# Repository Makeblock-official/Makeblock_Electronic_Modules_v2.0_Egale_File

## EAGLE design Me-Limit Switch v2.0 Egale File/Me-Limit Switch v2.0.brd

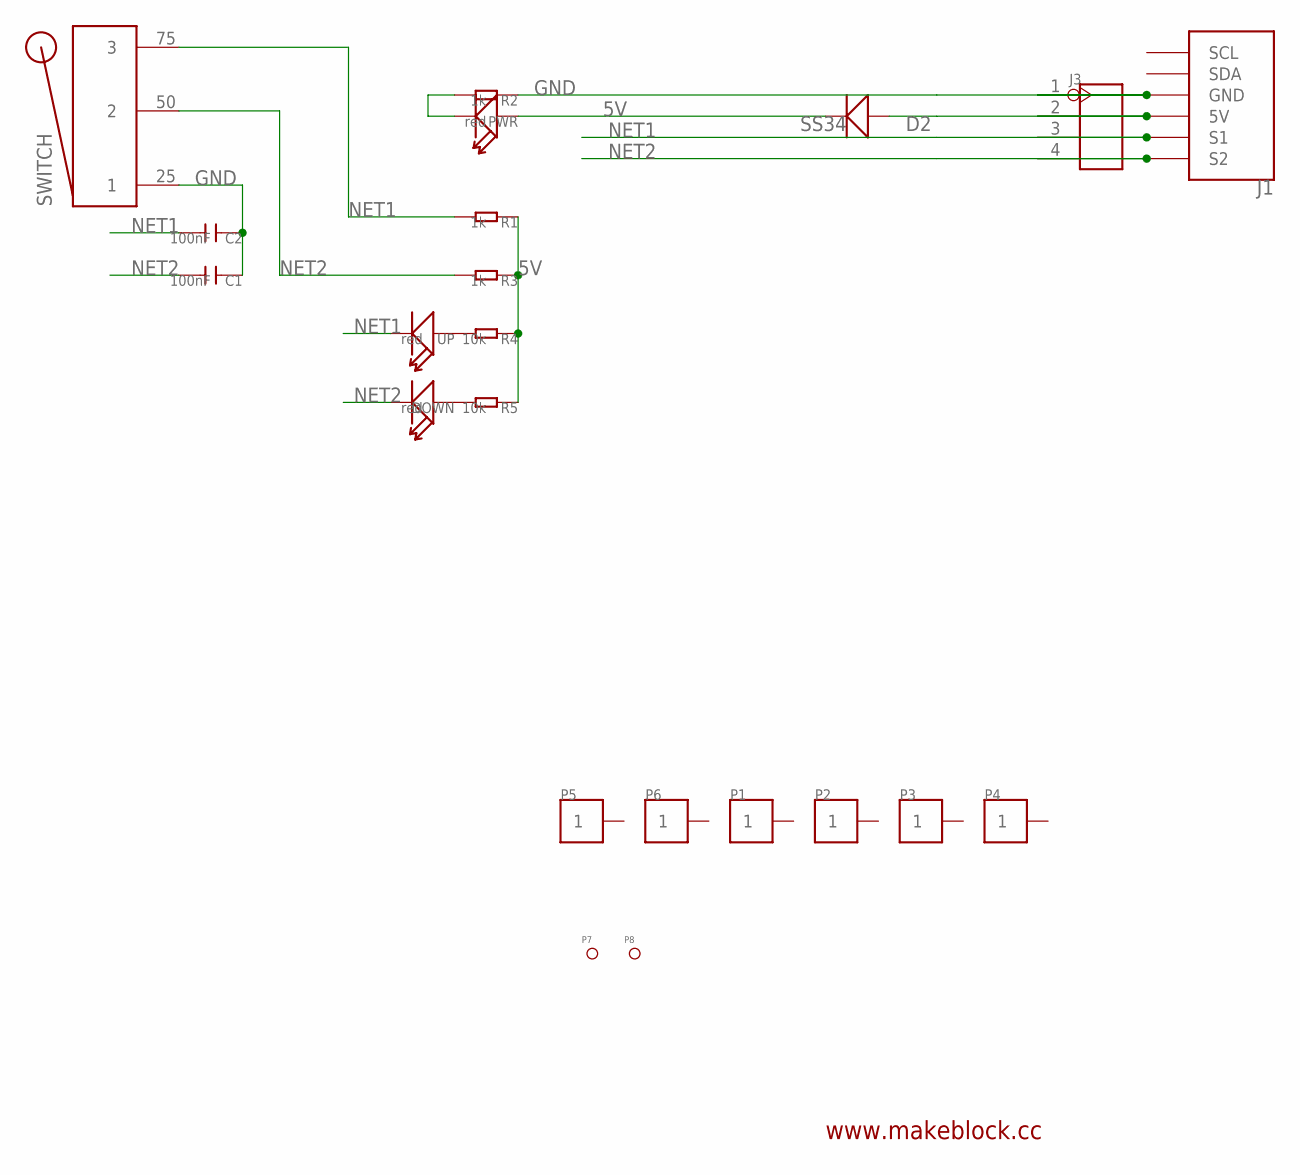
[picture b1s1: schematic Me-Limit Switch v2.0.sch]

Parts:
C1, C2: 100nF; 0603
D2: SS34; D2010
DOWN: red; LED-0603
J1: RJ11-6P6C-DIGI; RJ11-6P6C
J3: HEADER-4P-60/35MIL; 4P-65/35MIL
P1, P2, P3, P4, P5, P6: PAD-1P-4MM; HOLE-01
P7, P8: PAD-MARK; ROUND-MARK-1.0
PWR: red; LED-0603
R1, R2, R3: 1k; 0603
R4, R5: 10k; 0603
SWITCH: OMRON-SS5GL2
UP: red; LED-0603

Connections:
5V: D2.-, PWR.+, R1.1, R3.1, R4.1, R5.1
GND: C1.1, C2.1, J1.3 (GND), J3.1, R2.1, SWITCH.25 (1)
unnamed: PWR.-, R2.2
unnamed: DOWN.+, R5.2
unnamed: R4.2, UP.+
unnamed: D2.+, J1.4 (5V), J3.2
NET1: C2.2, J1.5 (S1), J3.3, R1.2, SWITCH.75 (3), UP.-
NET2: C1.2, DOWN.-, J1.6 (S2), J3.4, R3.2, SWITCH.50 (2)

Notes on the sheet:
www.makeblock.cc

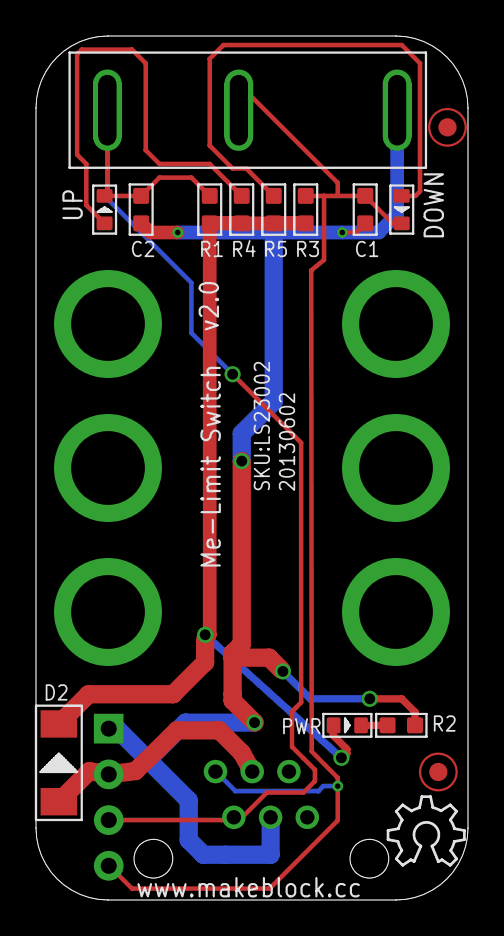
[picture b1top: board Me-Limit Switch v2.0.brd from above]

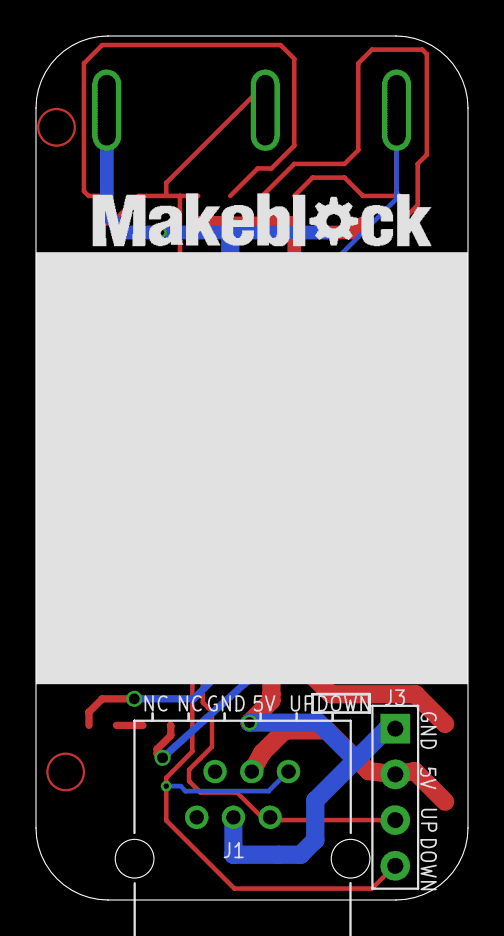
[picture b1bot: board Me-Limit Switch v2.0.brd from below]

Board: 2 copper layers, 24.0 x 48.0 mm, 24 parts (3 on the bottom side), 8 nets.

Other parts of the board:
U$1: LOGO-3/2
U$2: OSHW_6X150_NOTEXT

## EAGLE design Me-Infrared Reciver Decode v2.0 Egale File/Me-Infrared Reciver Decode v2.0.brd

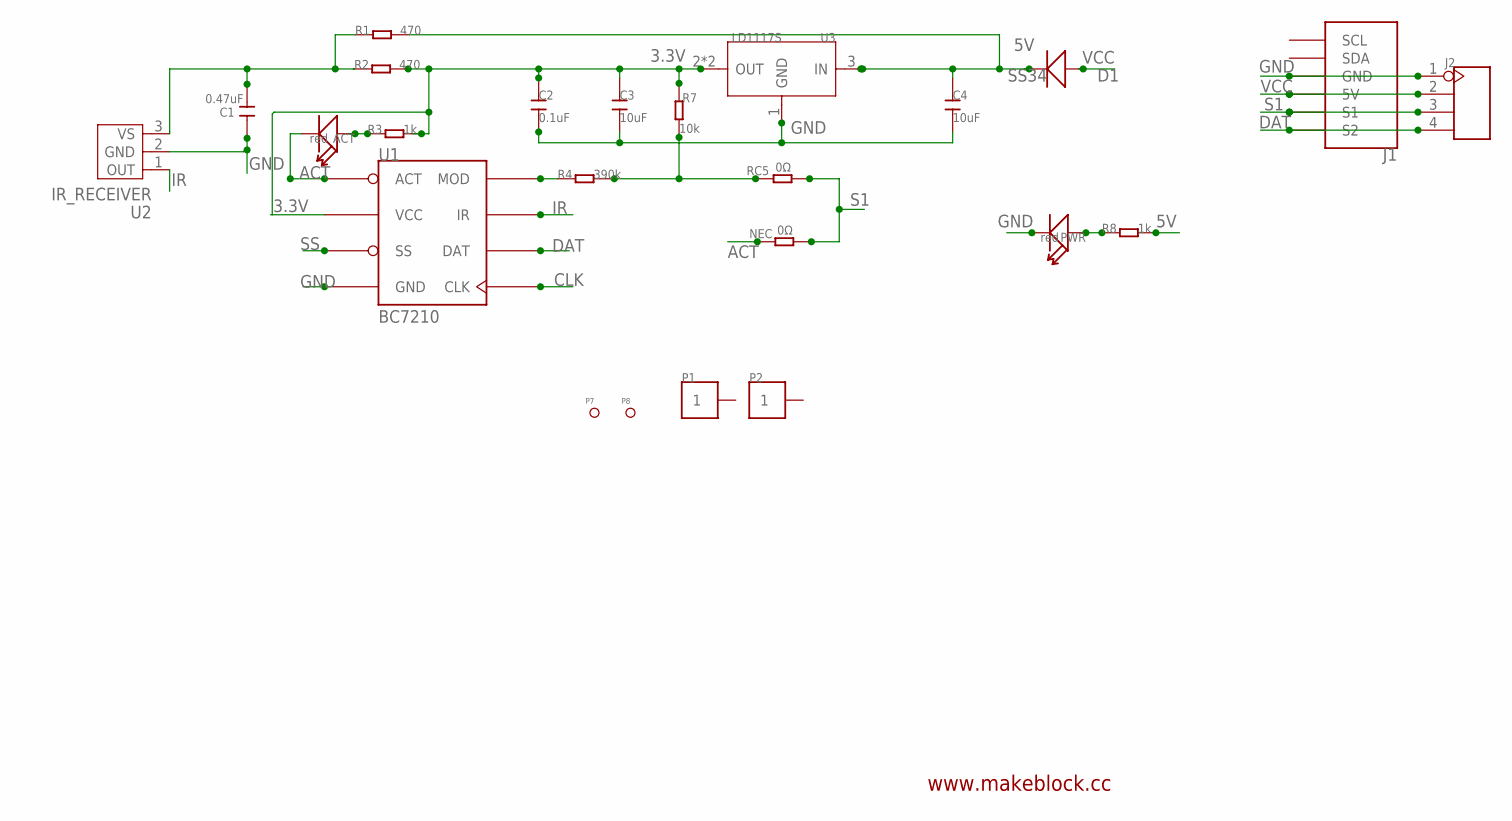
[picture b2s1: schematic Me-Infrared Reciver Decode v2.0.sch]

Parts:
ACT: red; LED-0603
C1: 0.47uF; 0603
C2: 0.1uF; 0603
C3, C4: 10uF; 0603
D1: SS34; D2010
J1: RJ11-6P6C-DIGI; RJ11-6P6C
J2: HEADER-4P-60/35MIL; 4P-65/35MIL
NEC: 0Ω; 0603
P1, P2: PAD-1P-4MM; HOLE-01
P7, P8: PAD-MARK; ROUND-MARK-1.0
PWR: red; LED-0603
R1, R2: 470; 0603
R3, R8: 1k; 0603
R4: 390k; 0603
R7: 10k; 0603
RC5: 0Ω; 0603
U1: BC7210
U2: IR_RECEIVER
U3: LD1117S; SOT-223

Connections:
3.3V: C2.1, C3.1, R2.2, R3.2, R7.2, U1.P$2 (VCC), U3.2 (OUT), U3.TER (OUT)
5V: C4.1, D1.-, R1.2, R8.2, U3.3 (IN)
ACT: ACT.-, NEC.1, U1.P$1 (ACT)
CLK: U1.P$5 (CLK)
DAT: J1.6 (S2), J2.4, U1.P$6 (DAT)
GND: C1.1, C2.2, C3.2, C4.2, J1.3 (GND), J2.1, PWR.-, U1.P$4 (GND), U2.2 (GND), U3.1 (GND)
IR: U1.P$7 (IR), U2.1 (OUT)
unnamed: R4.1, U1.P$8 (MOD)
unnamed: PWR.+, R8.1
unnamed: C1.2, R1.1, R2.1, U2.3 (VS)
unnamed: R4.2, R7.1, RC5.1
unnamed: ACT.+, R3.1
S1: J1.5 (S1), J2.3, NEC.2, RC5.2
SS: U1.P$3 (SS)
VCC: D1.+, J1.4 (5V), J2.2

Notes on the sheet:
www.makeblock.cc

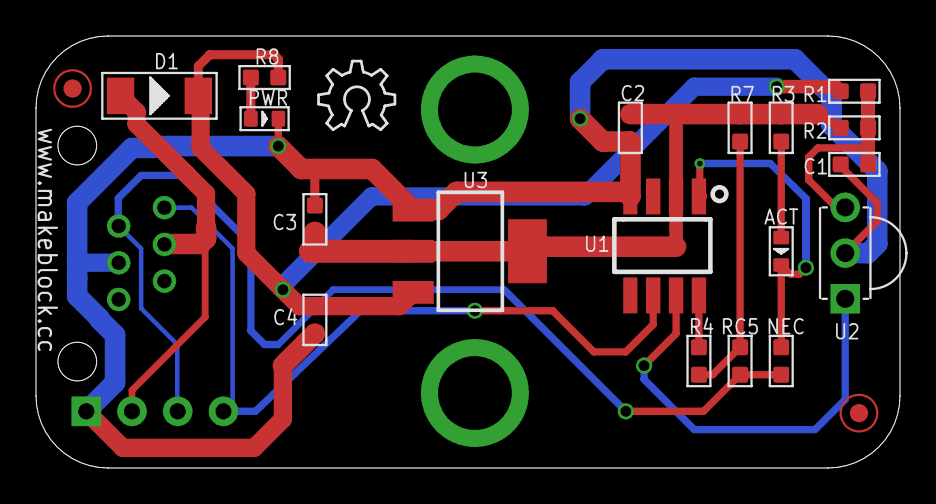
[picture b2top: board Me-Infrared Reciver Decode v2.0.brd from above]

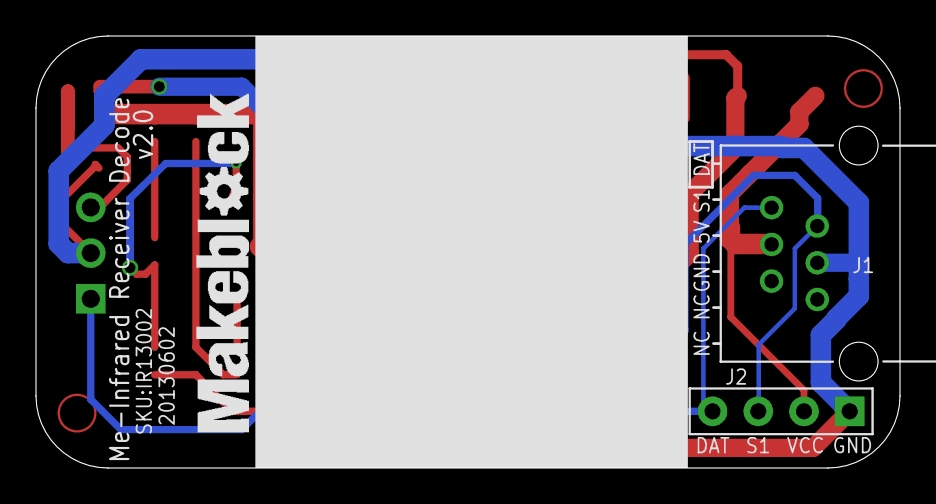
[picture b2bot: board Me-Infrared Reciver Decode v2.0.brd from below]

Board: 2 copper layers, 48.0 x 24.0 mm, 26 parts (3 on the bottom side), 13 nets.

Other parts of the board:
U$1: OSHW_6X150_NOTEXT
U$2: LOGO-3/2

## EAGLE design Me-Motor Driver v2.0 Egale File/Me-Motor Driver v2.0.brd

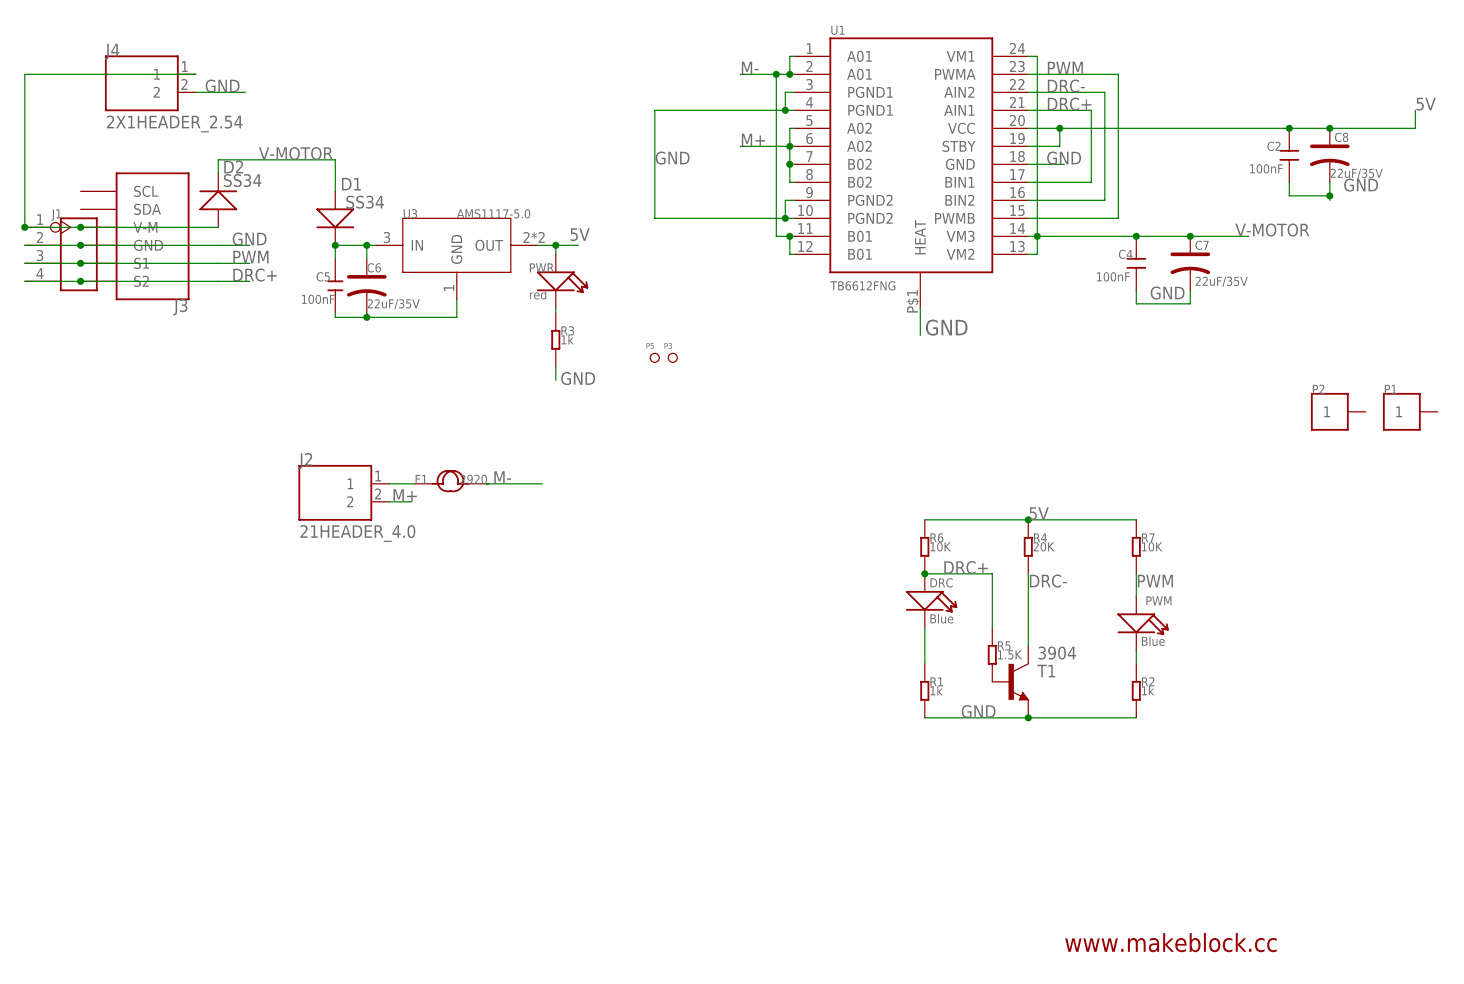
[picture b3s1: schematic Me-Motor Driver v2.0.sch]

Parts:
C2, C4: 100nF; 0603_S
C5: 100nF; 0603
C6, C7, C8: 22uF/35V; ELECTRO-SMD-B-4.8MM
D1, D2: SS34; D2010
DRC: Blue; LED-0603
F1: 2920
J1: HEADER-4P-60/35MIL; 4P-65/35MIL
J2: 21HEADER_4.0; 2*1HEADER_4.0
J3: RJ11-6P6C-MOTOR; RJ11-6P6C
J4: 2X1HEADER_2.54
P1, P2: PAD-1P-4MM; HOLE-01
P3: PAD-MARK; ROUND-MARK-1.0; PARTNO DNP
P5: PAD-MARK; ROUND-MARK-1.0
PWM: Blue; LED-0603
PWR: red; LED-0603
R1, R2, R3: 1k; 0603
R4: 20K; 0603
R5: 1.5K; 0603
R6, R7: 10K; 0603
T1: 3904
U1: TB6612FNG; SSOP24
U3: AMS1117-5.0; SOT-223

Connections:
5V: C2.1, C8.+, PWR.+, R4.1, R6.1, R7.1, U1.19 (STBY), U1.20 (VCC), U3.2 (OUT), U3.TER (OUT)
DRC+: DRC.+, J1.4, J3.6 (S2), R5.1, R6.2, U1.17 (BIN1), U1.21 (AIN1)
DRC-: R4.2, T1.3 (C), U1.16 (BIN2), U1.22 (AIN2)
GND: C2.2, C4.2, C5.1, C6.-, C7.-, C8.-, J1.2, J3.4 (GND), J4.2, R1.2, R2.2, R3.2, T1.2 (E), U1.3 (PGND1), U1.4 (PGND1), U1.9 (PGND2), U1.10 (PGND2), U1.18 (GND), U1.P$1 (HEAT), U3.1 (GND)
M+: J2.2, U1.5 (A02), U1.6 (A02), U1.7 (B02), U1.8 (B02)
M-: F1.2, U1.1 (A01), U1.2 (A01), U1.11 (B01), U1.12 (B01)
unnamed: DRC.-, R1.1
unnamed: F1.1, J2.1
unnamed: PWM.-, R2.1
unnamed: R5.2, T1.1 (B)
unnamed: PWR.-, R3.1
unnamed: C5.2, C6.+, D1.-, U3.3 (IN)
POWER: D2.+, J1.1, J3.3 (V-M), J4.1
PWM: J1.3, J3.5 (S1), PWM.+, R7.2, U1.15 (PWMB), U1.23 (PWMA)
V-MOTOR: C4.1, C7.+, D1.+, D2.-, U1.13 (VM2), U1.14 (VM3), U1.24 (VM1)

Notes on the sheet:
www.makeblock.cc

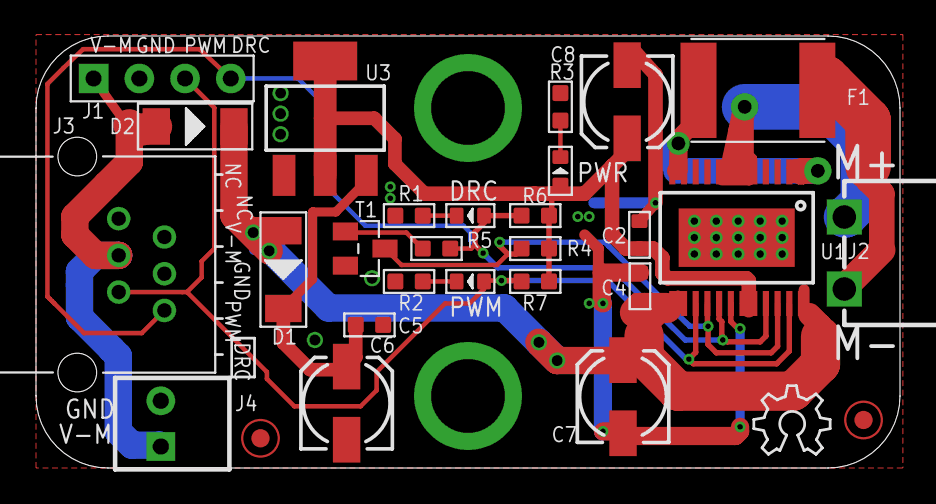
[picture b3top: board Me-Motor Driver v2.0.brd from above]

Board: 2 copper layers, 48.0 x 24.0 mm, 32 parts (1 on the bottom side), 15 nets.

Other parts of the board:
U$1: OSHW_6X150_NOTEXT
U$2: LOGO-3/2

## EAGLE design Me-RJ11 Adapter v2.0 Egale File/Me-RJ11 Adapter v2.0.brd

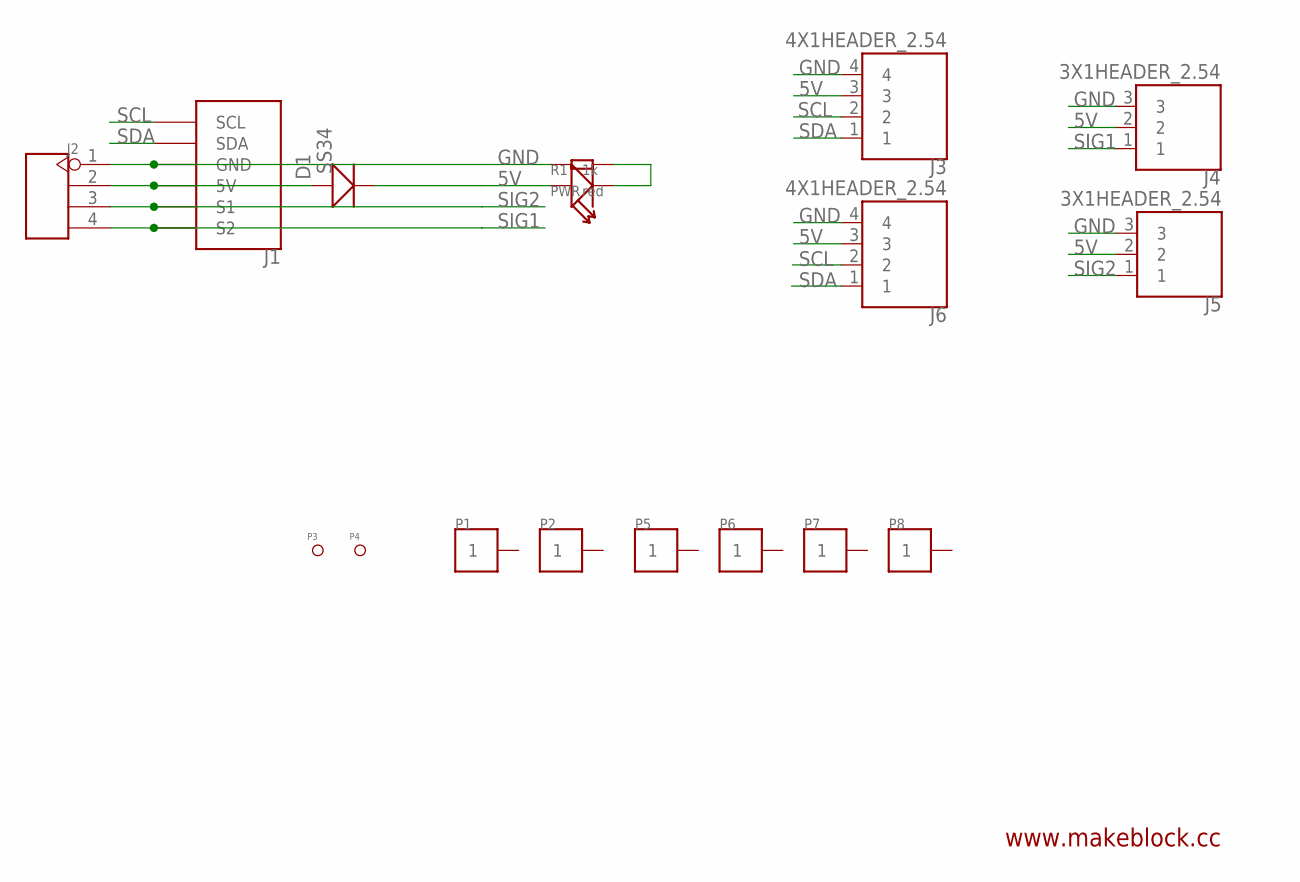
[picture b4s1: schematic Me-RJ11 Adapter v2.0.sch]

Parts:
D1: SS34; D2010
J1: RJ11-6P6C-DIGI; RJ11-6P6C
J2: HEADER-4P-60/35MIL; 4P-65/35MIL
J3, J6: 4X1HEADER_2.54
J4, J5: 3X1HEADER_2.54
P1, P2, P5, P6, P7, P8: PAD-1P-4MM; HOLE-01
P3, P4: PAD-MARK; ROUND-MARK-1.0
PWR: red; LED-0603
R1: 1k; 0603

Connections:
5V: D1.-, J3.3, J4.2, J5.2, J6.3, PWR.+
GND: J1.3 (GND), J2.1, J3.4, J4.3, J5.3, J6.4, R1.1
unnamed: PWR.-, R1.2
unnamed: D1.+, J1.4 (5V), J2.2
SCL: J1.1 (SCL), J3.2, J6.2
SDA: J1.2 (SDA), J3.1, J6.1
SIG1: J1.6 (S2), J2.4, J4.1
SIG2: J1.5 (S1), J2.3, J5.1

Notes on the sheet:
www.makeblock.cc

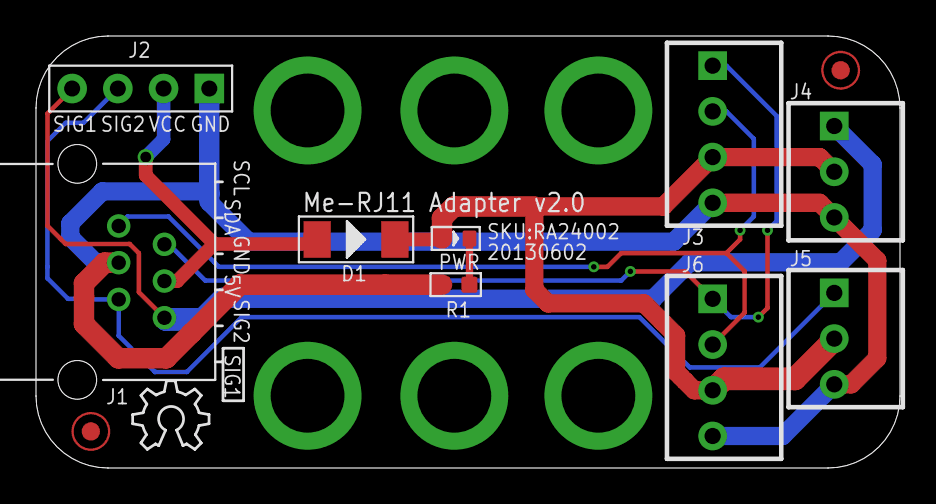
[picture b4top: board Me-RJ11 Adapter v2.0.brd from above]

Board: 2 copper layers, 48.0 x 24.0 mm, 19 parts (1 on the bottom side), 8 nets.

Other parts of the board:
U$1: LOGO-3/2
U$2: OSHW_6X150_NOTEXT

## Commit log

2013-08-26 Makeblock Electronic Modules v2.0 Eagle Files

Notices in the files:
parts and their libraries:
SparkFun-PowerIC: Licensing: CC v3.0 Share-Alike You are welcome to use this library for commercial purposes.
